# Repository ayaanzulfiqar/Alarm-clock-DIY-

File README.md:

# Alarm-clock-DIY-
Custom esp32 alarm clock with 4 switch buttons with a buzzer

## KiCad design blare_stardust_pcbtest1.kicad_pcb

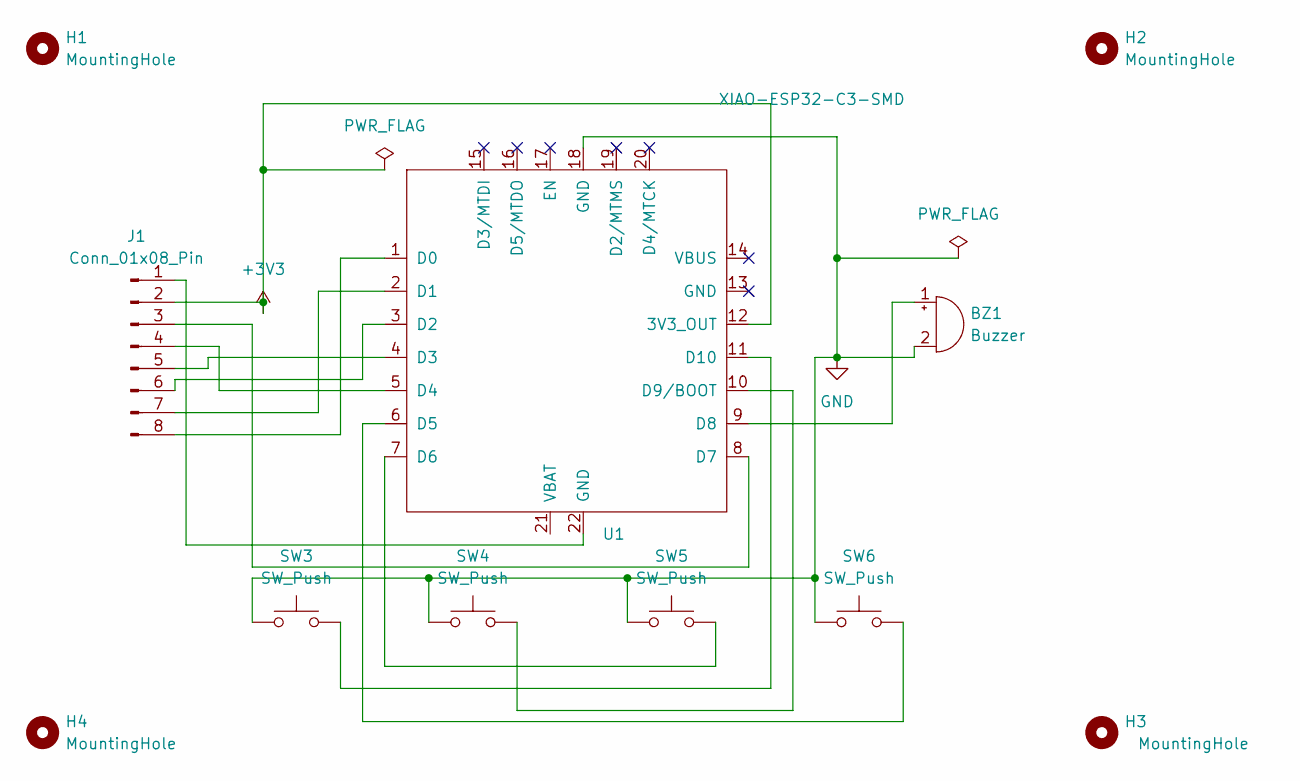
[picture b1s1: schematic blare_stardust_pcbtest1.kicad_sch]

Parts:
BZ1: Buzzer; Buzzer_12x9.5RM7.6
H1, H2, H3, H4: MountingHole; MountingHole_3.2mm_M3
J1: Conn_01x08_Pin; PinHeader_1x08_P2.54mm_Vertical
SW3, SW4, SW5, SW6: SW_Push; SW_Cherry_MX_1.00u_PCB
U1: XIAO-ESP32-C3-SMD

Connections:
+3V3: J1.2, U1.12 (3V3_OUT)
GND: BZ1.2 (-), SW3.1, SW4.1, SW5.1, SW6.1, U1.18 (GND)
unnamed: BZ1.1 (+), U1.9 (D8)
unnamed: J1.1, U1.22 (GND)
unnamed: J1.3, U1.8 (D7)
unnamed: J1.4, U1.5 (D4)
unnamed: J1.5, U1.4 (D3)
unnamed: J1.6, U1.3 (D2)
unnamed: J1.7, U1.2 (D1)
unnamed: J1.8, U1.1 (D0)
unnamed: SW6.2, U1.6 (D5)
unnamed: SW5.2, U1.7 (D6)
unnamed: SW4.2, U1.10 (D9/BOOT)
unnamed: SW3.2, U1.11 (D10)

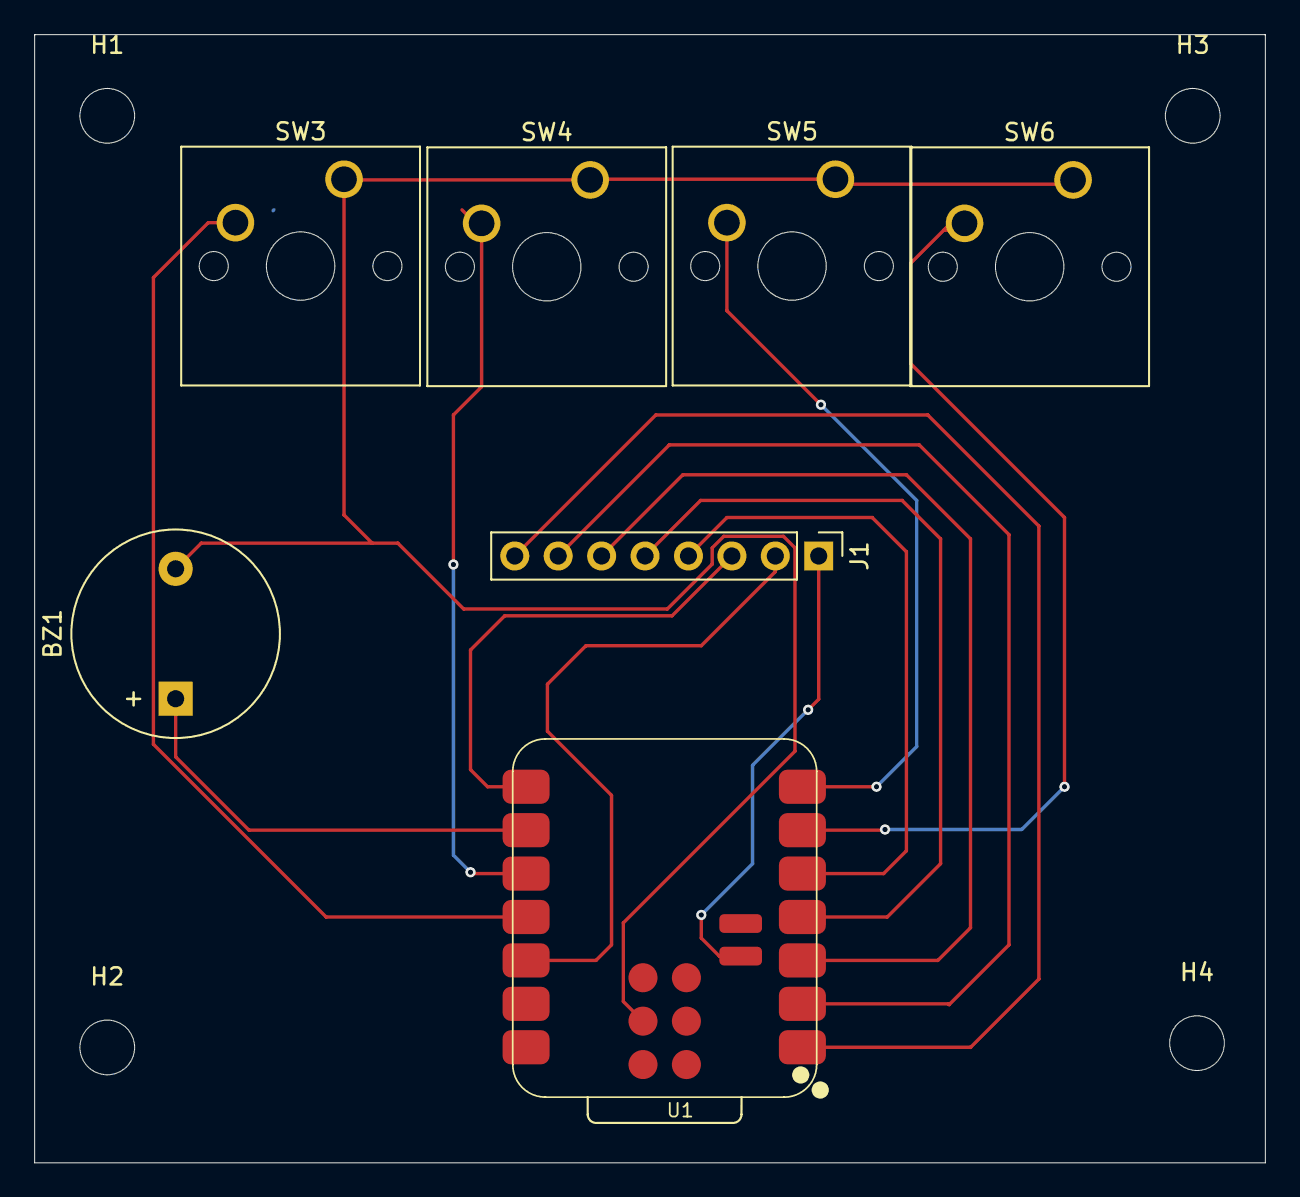
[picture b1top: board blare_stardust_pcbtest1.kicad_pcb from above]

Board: 2 copper layers, 72.0 x 66.0 mm, 11 parts (0 on the bottom side), 14 nets.
